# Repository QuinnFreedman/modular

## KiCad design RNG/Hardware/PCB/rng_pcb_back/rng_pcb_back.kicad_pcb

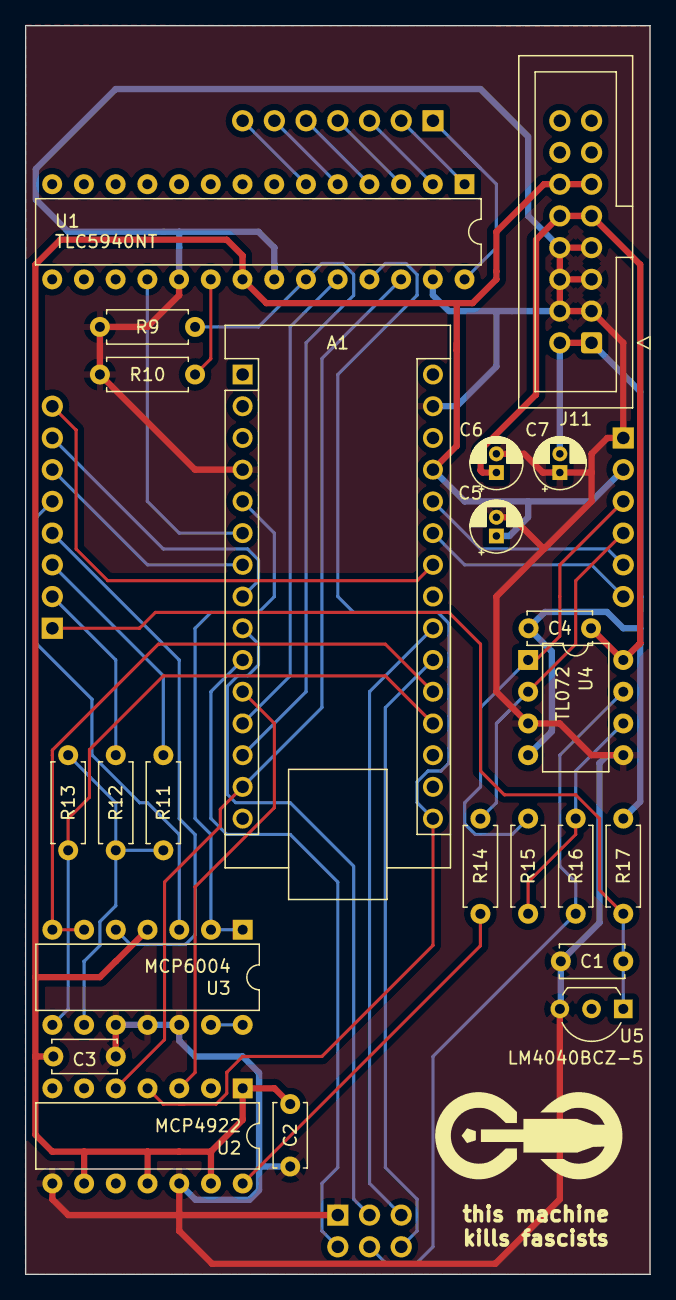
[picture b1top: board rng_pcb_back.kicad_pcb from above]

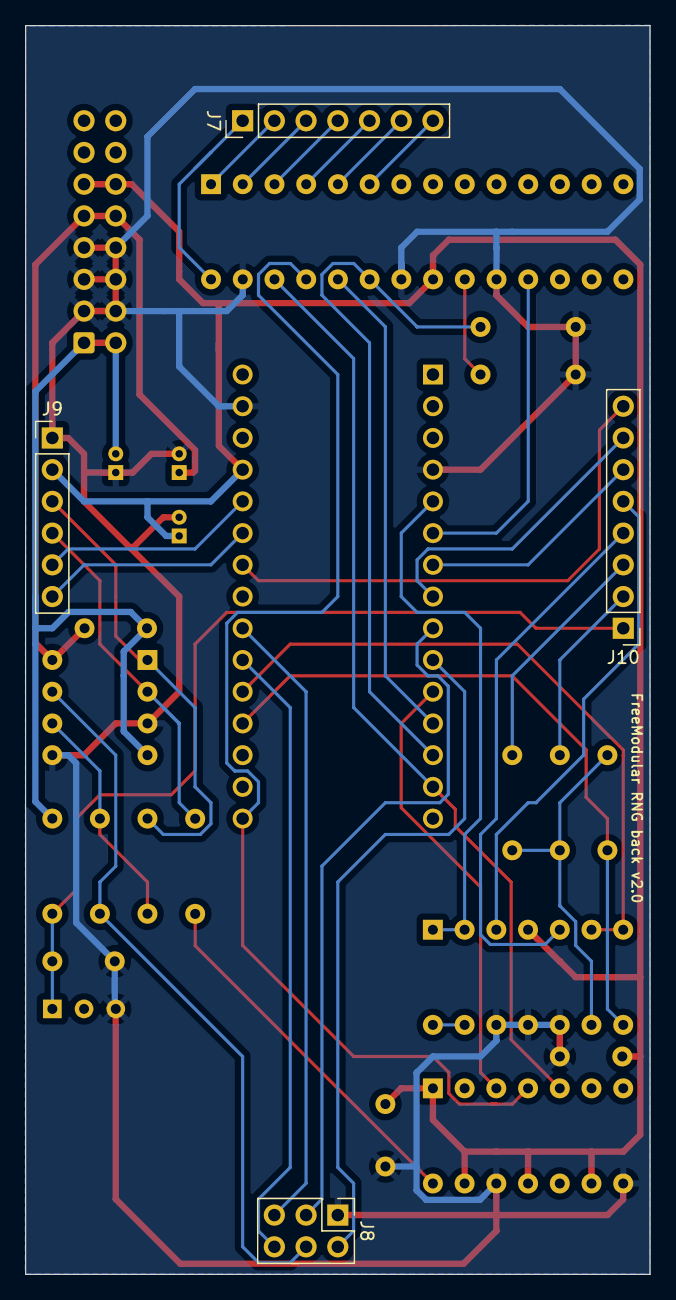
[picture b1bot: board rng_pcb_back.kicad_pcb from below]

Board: 2 copper layers, 50.0 x 100.0 mm, 27 parts (4 on the bottom side), 42 nets.

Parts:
A1: Arduino_Nano_v3.x; Arduino_Nano
C1, C2, C3, C4: 100nF; C_Disc_D5.0mm_W2.5mm_P5.00mm
C5, C6, C7: 10uF; CP_Radial_D4.0mm_P1.50mm
J7: Conn_01x07_Socket; PinHeader_1x07_P2.54mm_Vertical
J8: Conn_02x03_Socket; PinHeader_2x03_P2.54mm_Vertical
J9: Conn_01x06_Socket; PinHeader_1x06_P2.54mm_Vertical
J10: Conn_01x08_Socket; PinHeader_1x08_P2.54mm_Vertical
J11: Eurorack_2x8_Power; IDC-Header_2x08_P2.54mm_Vertical
R9, R10, R11, R12, R13, R16: 100kΩ; R_Axial_DIN0207_L6.3mm_D2.5mm_P7.62mm_Horizontal
R14, R15: 50kΩ; R_Axial_DIN0207_L6.3mm_D2.5mm_P7.62mm_Horizontal
R17: 470Ω; R_Axial_DIN0207_L6.3mm_D2.5mm_P7.62mm_Horizontal
U1: TLC5940NT; DIP-28_W7.62mm
U2: MCP4922; DIP-14_W7.62mm
U3: MCP6004; DIP-14_W7.62mm
U4: TL072; DIP-8_W7.62mm
U5: LM4040BCZ-5; TO-92L_Inline_Wide

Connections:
+5V: A1.27 (+5V), C2.1, C3.1, C5.1, J9.2, J11.11 (+5v), J11.12 (+5v), U1.21 (VCC), U2.1 (Vdd), U2.9 (~SHDN), U2.11 (VrefB), U2.13 (VrefA), U3.4 (V+)
+12V: C4.1, C6.1, J11.9 (+12v), J11.10 (+12v), U4.8 (V+)
-12V: C4.2, C7.2, J11.1 (-12v), J11.2 (-12v), R17.1, U4.4 (V-)
CV_BIAS: A1.19 (A0), R13.2, U3.8
CV_CLOCK: A1.5 (D2), U3.1, U3.2 (-)
CV_ENABLE: A1.20 (A1), U3.6 (-), U3.7
DAC_CS: A1.11 (D8), U2.3 (~CS)
DAC_OUT: R14.1, U2.14 (VA)
ENABLED_LED: A1.21 (A2), J8.6
GAIN_A: J9.4, R14.2, U4.2 (-)
GAIN_B: J9.3, R15.1, U4.1
GATE_A_OUT: A1.10 (D7), J8.2
GATE_B_OUT: A1.9 (D6), J8.3
GND: A1.4 (GND), A1.29 (GND), C1.2, C2.2, C3.2, C5.2, C6.2, C7.1, J8.1, J9.1, J11.3 (GND), J11.4 (GND), J11.5 (GND), J11.6 (GND), J11.7 (GND), J11.8 (GND), R9.2, R10.2, U1.19 (DCPRG), U1.22 (GND), U1.27 (VPRG), U2.8 (~LDAC), U2.12 (Vss), U3.10 (+), U3.11 (V-), U3.12 (+), U4.3 (+), U4.5 (+), U5.3 (K)
INPUT_CV_BIAS: J10.3, R11.1
INPUT_CV_CLOCK: J10.5, U3.3 (+)
INPUT_CV_ENABLE: J10.4, U3.5 (+)
LED_BLANK: A1.13 (D10), R9.1, U1.23 (BLANK)
LED_LATCH: A1.12 (D9), U1.24 (XLAT)
LED_PWM_REF: A1.6 (D3), U1.18 (GSCLK)
unnamed: J7.1, U1.28 (OUT0)
unnamed: J7.2, U1.1 (OUT1)
unnamed: J7.3, U1.2 (OUT2)
unnamed: J7.4, U1.3 (OUT3)
unnamed: J7.5, U1.4 (OUT4)
unnamed: J7.6, U1.5 (OUT5)
unnamed: J7.7, U1.6 (OUT6)
unnamed: R10.1, U1.20 (IREF)
unnamed: R11.2, R12.2, R13.1, U3.9 (-)
unnamed: U3.13 (-), U3.14
unnamed: R15.2, R16.1, U4.6 (-)
POT_BIAS: J10.2, R12.1
POT_RANDOM: A1.26 (A7), J9.5
RANDOM_OUT: J8.4, R16.2, U4.7
RE_A: A1.8 (D5), J10.7
RE_B: A1.7 (D4), J10.6
RE_SWITCH: A1.24 (A5), J10.8
SPI_MOSI: A1.14 (D11), U1.26 (SIN), U2.5 (SDI)
SPI_SCK: A1.16 (D13), U1.25 (SCLK), U2.4 (SCK)
TRIG_IN_LED: A1.22 (A3), J8.5
TRIG_SWTICH: A1.25 (A6), J9.6
VREF_-5: C1.1, J10.1, R17.2, U5.1 (A)

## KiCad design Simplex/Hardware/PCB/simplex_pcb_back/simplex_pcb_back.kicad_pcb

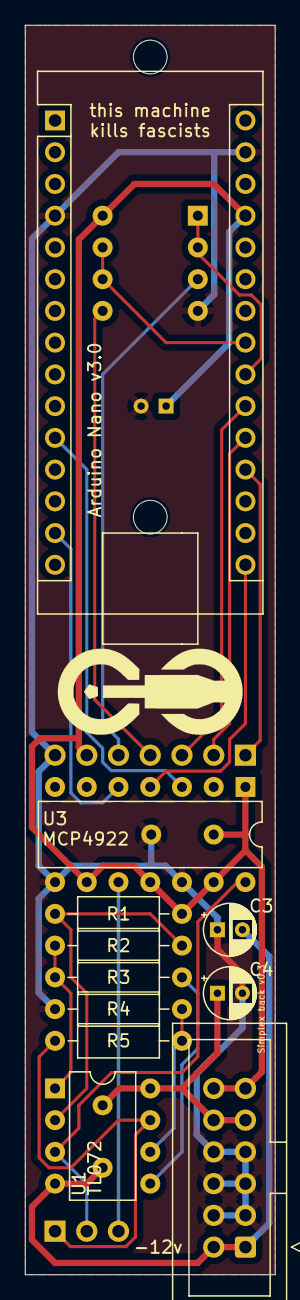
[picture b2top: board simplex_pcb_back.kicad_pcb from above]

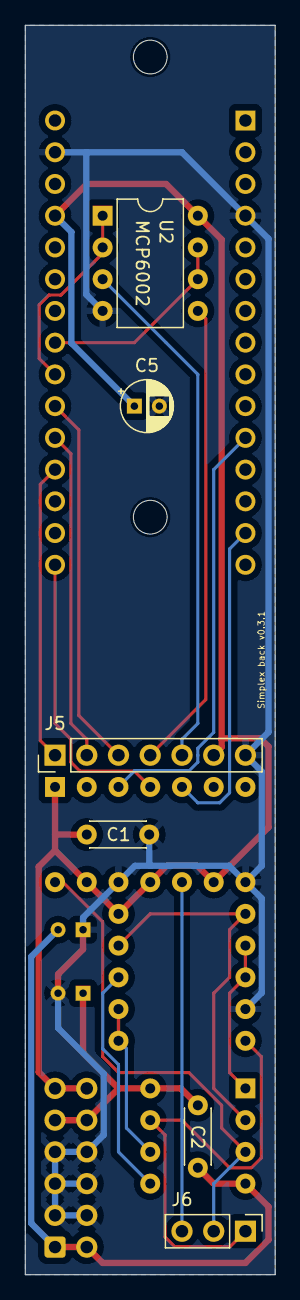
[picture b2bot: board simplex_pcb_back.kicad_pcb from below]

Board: 2 copper layers, 20.0 x 100.0 mm, 19 parts (6 on the bottom side), 21 nets.

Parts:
A1: Arduino_Nano_v3.x; Arduino_Nano
C1, C2: 100nF; C_Disc_D4.3mm_W1.9mm_P5.00mm
C3, C4, C5: 10uF; CP_Radial_D4.0mm_P2.00mm
H1, H2: MountingHole; MountingHole_2.7mm_M2.5
J1: Conn_02x06_Odd_Even; IDC-Header_2x06_P2.54mm_Vertical
J5: Conn_01x07_Male; PinHeader_1x07_P2.54mm_Vertical
J6: Conn_01x03_Male; PinHeader_1x03_P2.54mm_Vertical
R1, R2, R3, R4, R5: 10kΩ; R_Axial_DIN0207_L6.3mm_D2.5mm_P10.16mm_Horizontal
U1: TL072; DIP-8_W7.62mm
U2: MCP6002-xP; DIP-8_W7.62mm
U3: MCP4922; DIP-14_W7.62mm

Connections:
+5V: A1.27 (+5V), C1.1, C5.1, J1.11, J1.12, J5.6, R1.2, U2.8 (V+), U3.1 (Vdd), U3.9 (~SHDN), U3.11 (VrefB), U3.13 (VrefA)
+12V: C2.1, C4.1, J1.9, J1.10, U1.8 (V+)
-12V: C2.2, C3.2, J1.1, J1.2, U1.4 (V-)
ATTEN_POT: A1.21 (A2), J5.3
DAC_CS: A1.11 (D8), U3.3 (~CS)
DAC_OUT_A: J6.2, U1.3 (+), U3.14 (VA)
GND: A1.4 (GND), A1.29 (GND), C1.2, C3.1, C4.2, C5.2, J1.3, J1.4, J1.5, J1.6, J1.7, J1.8, J5.7, R4.2, U2.4 (V-), U3.8 (~LDAC), U3.12 (Vss)
unnamed: A1.22 (A3), U2.1, U2.2 (-)
unnamed: A1.23 (A4), U2.6 (-), U2.7
unnamed: R2.1, R3.2, U1.1
unnamed: R1.1, R2.2, U1.2 (-)
unnamed: R3.1, U1.5 (+)
unnamed: R4.1, R5.2, U1.6 (-)
OUT_A: J6.1, R5.1, U1.7
OUT_B: J6.3, U3.10 (VB)
SPEED_CV: J5.5, U2.3 (+)
SPEED_POT: A1.19 (A0), J5.1
SPI_MOSI: A1.14 (D11), U3.5 (SDI)
SPI_SCK: A1.16 (D13), U3.4 (SCK)
TEXTURE_CV: J5.4, U2.5 (+)
TEXTURE_POT: A1.20 (A1), J5.2

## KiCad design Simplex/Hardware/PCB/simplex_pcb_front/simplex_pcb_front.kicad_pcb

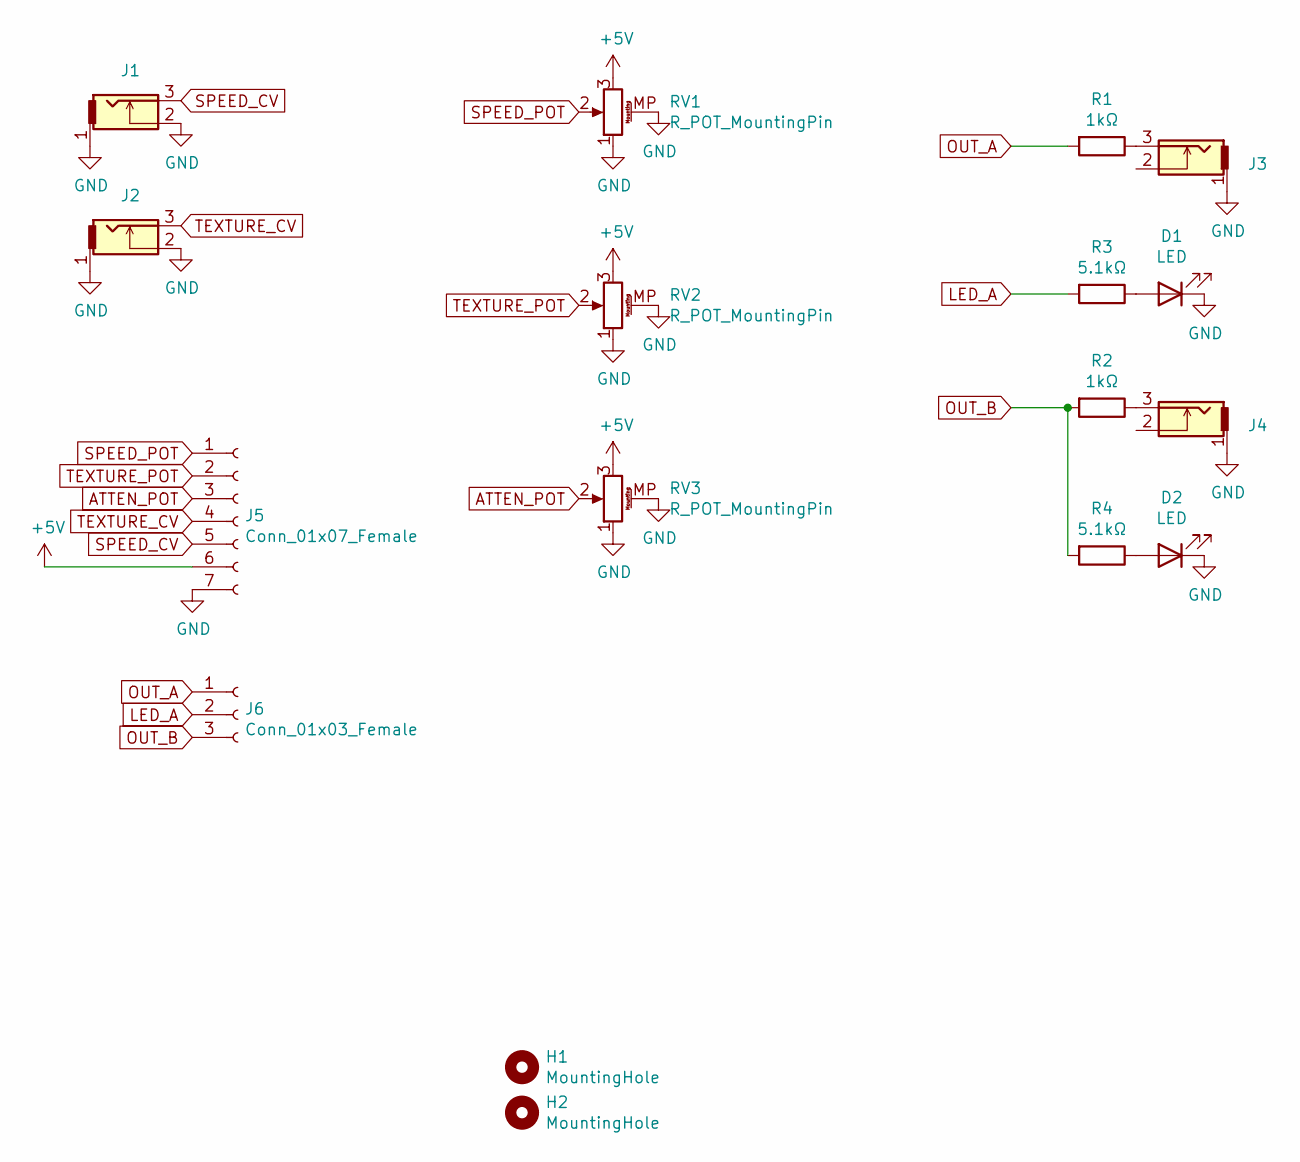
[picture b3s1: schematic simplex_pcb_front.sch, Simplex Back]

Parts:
D1, D2: LED; LED_D3.0mm
H1, H2: MountingHole; MountingHole_2.7mm
J1, J2, J3, J4: THONKICONN; THONKICONN_perf
J5: Conn_01x07_Female; PinSocket_1x07_P2.54mm_Vertical
J6: Conn_01x03_Female; PinSocket_1x03_P2.54mm_Vertical
R1, R2: 1kΩ; R_Axial_DIN0207_L6.3mm_D2.5mm_P10.16mm_Horizontal
R3, R4: 5.1kΩ; R_Axial_DIN0207_L6.3mm_D2.5mm_P10.16mm_Horizontal
RV1, RV2, RV3: R_POT_MountingPin; Alpha_Potentiometer_Grounded

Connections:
+5V: J5.6, RV1.3, RV2.3, RV3.3
ATTEN_POT: J5.3, RV3.2
GND: D1.1 (K), D2.1 (K), J1.1, J1.2, J2.1, J2.2, J3.1, J4.1, J5.7, RV1.1, RV1.MP (MountPin), RV2.1, RV2.MP (MountPin), RV3.1, RV3.MP (MountPin)
LED_A: J6.2, R3.2
unnamed: D1.2 (A), R3.1
unnamed: D2.2 (A), R4.1
unnamed: J3.3, R1.1
unnamed: J4.3, R2.1
OUT_A: J6.1, R1.2
OUT_B: J6.3, R2.2, R4.2
SPEED_CV: J1.3, J5.5
SPEED_POT: J5.1, RV1.2
TEXTURE_CV: J2.3, J5.4
TEXTURE_POT: J5.2, RV2.2

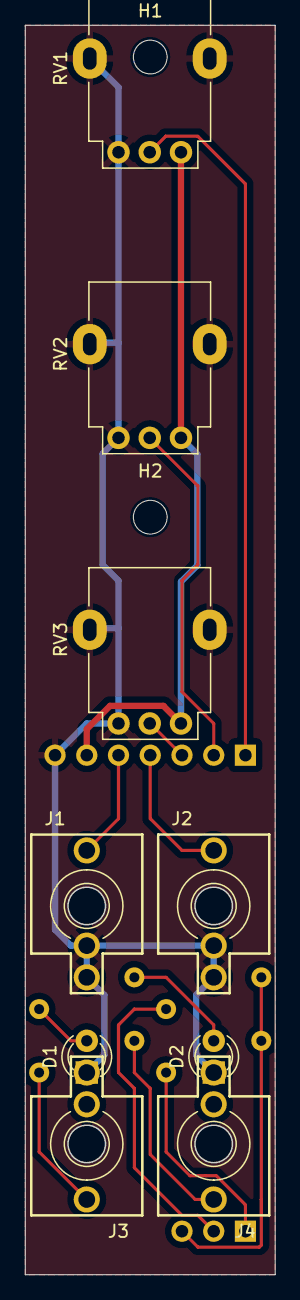
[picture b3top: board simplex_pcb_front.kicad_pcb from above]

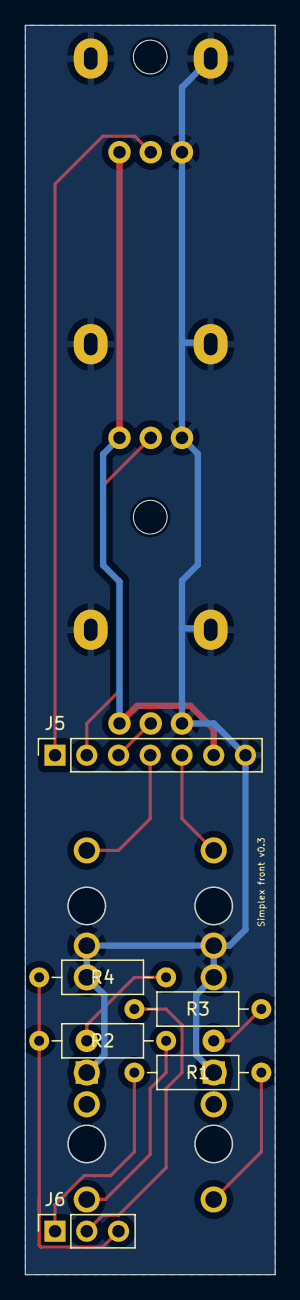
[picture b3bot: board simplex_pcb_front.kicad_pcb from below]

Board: 2 copper layers, 20.0 x 100.0 mm, 17 parts (6 on the bottom side), 14 nets.

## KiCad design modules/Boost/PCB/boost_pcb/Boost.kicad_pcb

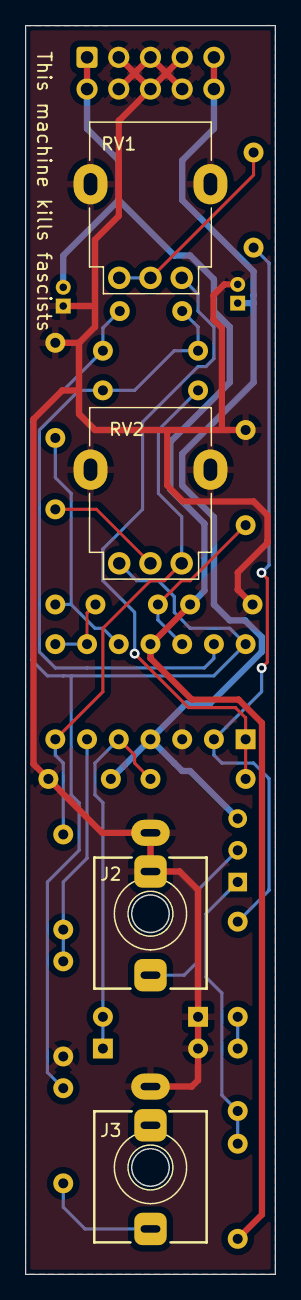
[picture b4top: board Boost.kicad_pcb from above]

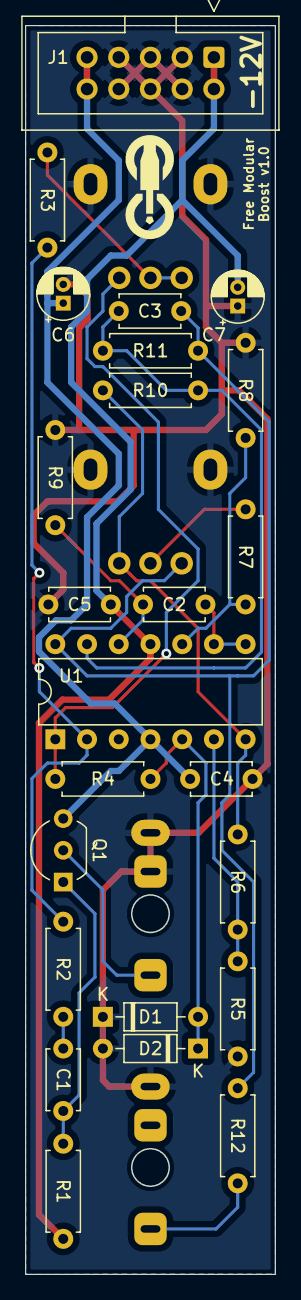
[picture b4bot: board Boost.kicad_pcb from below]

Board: 2 copper layers, 20.0 x 100.0 mm, 28 parts (24 on the bottom side), 19 nets.

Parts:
C1: 470nF; C_Disc_D4.7mm_W2.5mm_P5.00mm
C2: 1uF; C_Disc_D4.7mm_W2.5mm_P5.00mm
C3: 33pF; C_Disc_D4.7mm_W2.5mm_P5.00mm
C4, C5: 100nF; C_Disc_D4.7mm_W2.5mm_P5.00mm
C6, C7: 10uF; CP_Radial_D4.0mm_P1.50mm
D1, D2: 1N4148; D_DO-35_SOD27_P7.62mm_Horizontal
J1: 2x5 IDC; IDC-Header_2x05_P2.54mm_Vertical
J2, J3: THONKICONN
Q1: 2N3904; TO-92_Inline_Wide
R1, R4: 10k; R_Axial_DIN0207_L6.3mm_D2.5mm_P7.62mm_Horizontal
R2: 24k; R_Axial_DIN0207_L6.3mm_D2.5mm_P7.62mm_Horizontal
R3: 2.4k; R_Axial_DIN0207_L6.3mm_D2.5mm_P7.62mm_Horizontal
R5: 2k; R_Axial_DIN0207_L6.3mm_D2.5mm_P7.62mm_Horizontal
R6: 18k; R_Axial_DIN0207_L6.3mm_D2.5mm_P7.62mm_Horizontal
R7: 750k; R_Axial_DIN0207_L6.3mm_D2.5mm_P7.62mm_Horizontal
R8: 560k; R_Axial_DIN0207_L6.3mm_D2.5mm_P7.62mm_Horizontal
R9: 15k; R_Axial_DIN0207_L6.3mm_D2.5mm_P7.62mm_Horizontal
R10, R11: 100k; R_Axial_DIN0207_L6.3mm_D2.5mm_P7.62mm_Horizontal
R12: 1k; R_Axial_DIN0207_L6.3mm_D2.5mm_P7.62mm_Horizontal
RV1, RV2: 50k; Alpha_Potentiometer_Grounded
U1: TL074; DIP-14_W7.62mm

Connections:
+12V: C4.1, C6.1, J1.9 (+12v), J1.10 (+12v), Q1.3 (C), U1.4 (V+)
-12V: C5.2, C7.2, J1.1 (-12v), J1.2 (-12v), R1.2, U1.11 (V-)
GND: C4.2, C5.1, C6.2, C7.1, D1.1 (K), D2.2 (A), J1.3 (GND), J1.4 (GND), J1.5 (GND), J1.6 (GND), J1.7 (GND), J1.8 (GND), J2.1, J2.2, J3.1, R5.1, R8.2, R9.2, RV1.MP, RV2.MP, U1.3 (+)
unnamed: C1.2, R2.1
unnamed: C3.2, R11.1, R12.1, RV2.1, U1.14
unnamed: D1.2 (A), D2.1 (K), R4.2, U1.5 (+)
unnamed: J3.3, R12.2
unnamed: J2.3, Q1.2 (B)
unnamed: C1.1, Q1.1 (E), R1.1
unnamed: R3.2, RV1.1, RV1.2
unnamed: R4.1, RV1.3, U1.1
unnamed: R7.1, RV2.2
unnamed: R6.2, R10.2, RV2.3, U1.7
unnamed: R2.2, R3.1, U1.2 (-)
unnamed: R5.2, R6.1, U1.6 (-)
unnamed: R7.2, R8.1, U1.10 (+)
unnamed: C2.1, U1.8, U1.9 (-)
unnamed: C2.2, R9.1, U1.12 (+)
unnamed: C3.1, R10.1, R11.2, U1.13 (-)

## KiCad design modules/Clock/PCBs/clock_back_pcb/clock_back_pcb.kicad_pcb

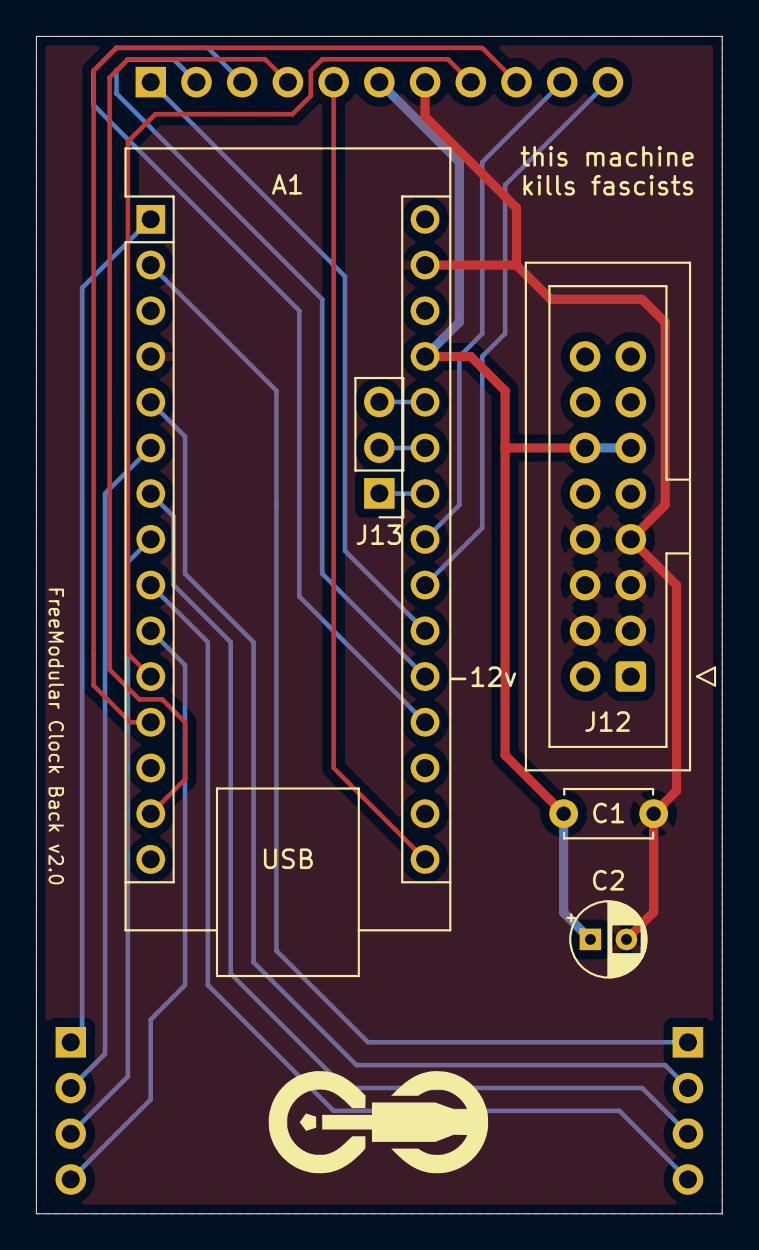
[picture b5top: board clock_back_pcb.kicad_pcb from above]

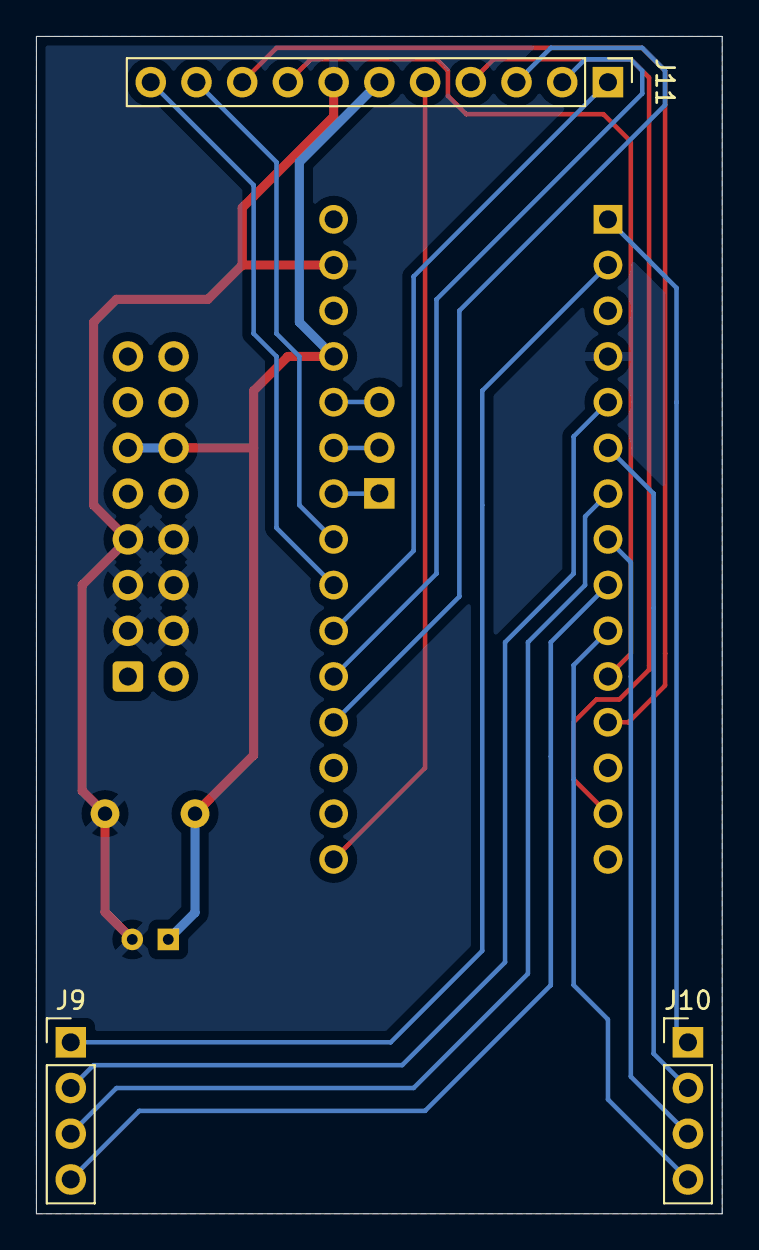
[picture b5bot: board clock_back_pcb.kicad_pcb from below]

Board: 2 copper layers, 38.1 x 65.4 mm, 9 parts (3 on the bottom side), 22 nets.

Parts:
A1: Arduino_Nano_v3.x; Arduino_Nano
C1: 100nF; C_Disc_D4.7mm_W2.5mm_P5.00mm
C2: 10uF; CP_Radial_D4.0mm_P2.00mm
G1: logo_small
J9, J10: Conn_01x04_Pin; PinHeader_1x04_P2.54mm_Vertical
J11: Conn_01x11_Pin; PinHeader_1x11_P2.54mm_Vertical
J12: Eurorack_2x8_Power; IDC-Header_2x08_P2.54mm_Vertical
J13: Conn_01x03_Socket; PinHeader_1x03_P2.54mm_Vertical

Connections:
+5V: A1.27 (+5V), C1.1, C2.1, J11.6, J12.11 (+5v), J12.12 (+5v)
ENCODER_A: A1.11 (D8), J11.8
ENCODER_B: A1.12 (D9), J11.9
ENCODER_SWITCH: A1.23 (A4), J11.10
GND: A1.4 (GND), A1.29 (GND), C1.2, C2.2, J11.7, J12.3 (GND), J12.4 (GND), J12.5 (GND), J12.6 (GND), J12.7 (GND), J12.8 (GND)
unnamed: A1.24 (A5), J13.1
unnamed: A1.25 (A6), J13.2
unnamed: A1.26 (A7), J13.3
OUT_1: A1.2 (D0/RX), J9.1
OUT_2: A1.1 (D1/TX), J10.1
OUT_3: A1.5 (D2), J9.2
OUT_4: A1.6 (D3), J10.2
OUT_5: A1.7 (D4), J9.3
OUT_6: A1.8 (D5), J10.3
OUT_7: A1.9 (D6), J9.4
OUT_8: A1.10 (D7), J10.4
PAUSE_BTN: A1.22 (A3), J11.11
RESET: A1.19 (A0), J11.3
SPI_CS: A1.21 (A2), J11.1
SPI_DC: A1.20 (A1), J11.2
SPI_SCK: A1.16 (D13), J11.5
SPI_SDA: A1.14 (D11), J11.4
